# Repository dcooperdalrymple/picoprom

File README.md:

PicoPROM - DIP-EEPROM Programmer based on Raspberry Pi Pico
===========================================================

Writes ROM images to parallel-interface EEPROMs via XMODEM file transfer over USB.

|  | |  |
|:----:|----|:----:|
| Pico connected to EEPROM | | Demo video on YouTube |

Warning
-------
The Raspberry Pi Pico is not 5V-tolerant, but these EEPROMs are 5V devices.
This is fine for write-only access, but it's important to ensure the EEPROM
never writes back to the Pico's GPIO pins.  **Make sure OE is permanently wired
high, to VCC, to prevent this.**

Features
--------

* No additional components are required - just the Pico and the EEPROM
* XMODEM+CRC transfer protocol makes it easy to send files to be written to the EEPROM
* Fast operation - comparable to TL866
* Supports paged writes as well as byte-writes
* Supports write protection

Not features
------------
* Reading back and verifying is not supported and probably won't ever be
* YMODEM, ZMODEM, and other XMODEM extensions aren't supported yet

Binary Installation
-------------------
1. Without an EEPROM connected, hold BOOTSEL and connect the Raspberry Pi Pico
2. Drag picoprom.uf2 into the Raspberry Pi Pico's mass storage window
3. It should then reboot and start communicating over USB Serial

Usage
-----
1. Disconnect the Raspberry Pi Pico from power/USB
2. Wire the Raspberry Pi Pico up to the EEPROM according to the pinout table below
3. Connect the Raspberry Pi Pico to the computer by USB
4. Launch a terminal app with XMODEM support, such as Tera Term, and connect it to the Raspberry Pi Pico
5. Verify that the Raspberry Pi Pico is reporting that it's ready to receive a ROM image
7. Use your terminal to send a ROM image using the XMODEM+CRC protocol
8. Disconnect power before removing the EEPROM from the circuit

Alternatively, instead of starting the XMODEM transfer, press Enter for some configuration options and follow the instructions.

Pinout
------
The pinout is quite straightforward - the pins are laid out around the Pico in almost 
the same arrangement that they appear on the EEPROM, to make it easy and tidy to wire up.

**Make sure OE is connected high, to VCC, as allowing it to float low could cause damage to your Pico.**

| Pico pin | EEPROM pin | Function |      | Pico pin | EEPROM pin | Function |
| -------- |:----------:| -------- | ---- | -------- |:----------:| -------- |
| GP3      | 1  | A14    | | VSYS     | 28 | VCC    |
| GP4      | 2  | A12    | | GND      | 27 | WE     |
| GP5      | 3  | A7     | | GP2      | 26 | A13    |
| GP6      | 4  | A6     | | GP28     | 25 | A8     |
| GP7      | 5  | A5     | | GP27     | 24 | A9     |
| GP8      | 6  | A4     | | GP26     | 23 | A11    |
| GP9      | 7  | A3     | | VSYS     | 22 | OE     |
| GP10     | 8  | A2     | | GP22     | 21 | A10    |
| GP11     | 9  | A1     | | GP21     | 20 | CE     |
| GP12     | 10 | A0     | | GP20     | 19 | D7     |
| GP13     | 11 | D0     | | GP19     | 18 | D6     |
| GP14     | 12 | D1     | | GP18     | 17 | D5     |
| GP15     | 13 | D2     | | GP17     | 16 | D4     |
| GND      | 14 | GND    | | GP16     | 15 | D3     |

### Other options

Depending upon preference, you could swap the CE and WE connections, or connect
them both to GP21.  It doesn't make any difference to the programming
operation, I just chose this layout because it seemed most convenient to me.

If you go further and change the GP pin numbering then you'll need to update
the corresponding array in `picoprom.c`.

Cloning and Building from Source
--------------------------------
1. Set up `pico-sdk` according to the Pico's getting-started guide.
2. Clone this repository alongside `pico-sdk`
3. Create a `build` folder
4. From within the `build` folder, type: `cmake ..`
5. From within the `build` folder, type: `make`

ROM Verification Support
------------------------

In order to verify EEPROM contents after writing, an octal bus transceiver
such as the 74HC245 must be used on the data bus between the Pico and the EEPROM.
The output enable and write enable pins must also be connected to GP0 and GP1 respectively.
The direction of this transceiver is controlled by the OE pin. Please refer to the
[included schematic](hardware/assets/schematic.pdf) for appropriate wiring.

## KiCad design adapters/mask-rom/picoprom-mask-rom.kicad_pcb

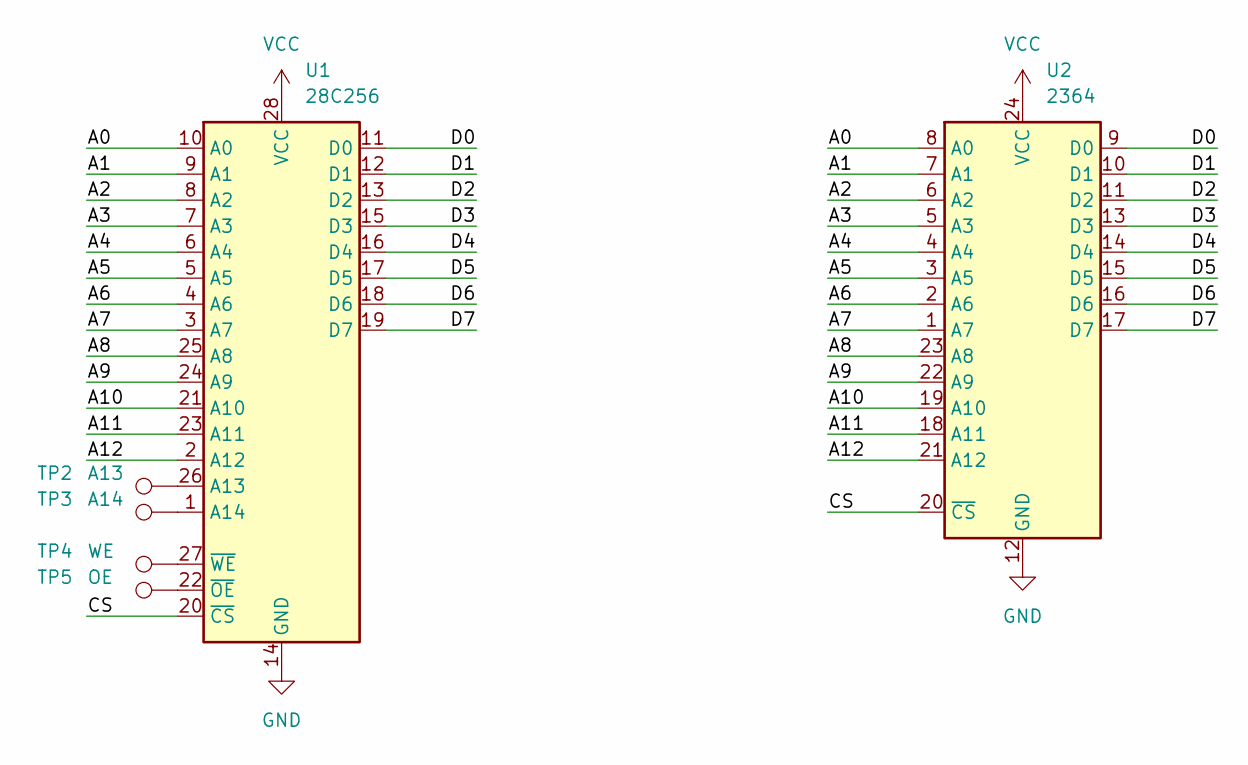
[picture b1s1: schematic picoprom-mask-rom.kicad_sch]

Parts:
TP2: A13; TestPoint_Pad_D1.0mm
TP3: A14; TestPoint_Pad_D1.0mm
TP4: WE; TestPoint_Pad_D1.0mm
TP5: OE; TestPoint_Pad_D1.0mm
U1: 28C256; PicoPROM_DIP-28_W15.24mm
U2: 2364; DIP-24_W15.24mm_Socket

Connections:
/A0: U1.10 (A0), U2.8 (A0)
/A1: U1.9 (A1), U2.7 (A1)
/A2: U1.8 (A2), U2.6 (A2)
/A3: U1.7 (A3), U2.5 (A3)
/A4: U1.6 (A4), U2.4 (A4)
/A5: U1.5 (A5), U2.3 (A5)
/A6: U1.4 (A6), U2.2 (A6)
/A7: U1.3 (A7), U2.1 (A7)
/A8: U1.25 (A8), U2.23 (A8)
/A9: U1.24 (A9), U2.22 (A9)
/A10: U1.21 (A10), U2.19 (A10)
/A11: U1.23 (A11), U2.18 (A11)
/A12: U1.2 (A12), U2.21 (A12)
/CS: U1.20 (~CS), U2.20 (~CS)
/D0: U1.11 (D0), U2.9 (D0)
/D1: U1.12 (D1), U2.10 (D1)
/D2: U1.13 (D2), U2.11 (D2)
/D3: U1.15 (D3), U2.13 (D3)
/D4: U1.16 (D4), U2.14 (D4)
/D5: U1.17 (D5), U2.15 (D5)
/D6: U1.18 (D6), U2.16 (D6)
/D7: U1.19 (D7), U2.17 (D7)
GND: U1.14 (GND), U2.12 (GND)
unnamed: TP2.1, U1.26 (A13)
unnamed: TP3.1, U1.1 (A14)
unnamed: TP5.1, U1.22 (~OE)
unnamed: TP4.1, U1.27 (~WE)
VCC: U1.28 (VCC), U2.24 (VCC)

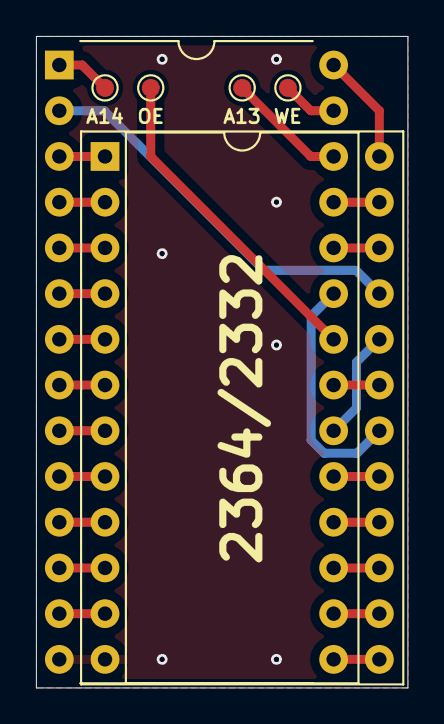
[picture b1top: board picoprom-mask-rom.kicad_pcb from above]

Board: 2 copper layers, 20.6 x 36.2 mm, 6 parts (0 on the bottom side), 28 nets.

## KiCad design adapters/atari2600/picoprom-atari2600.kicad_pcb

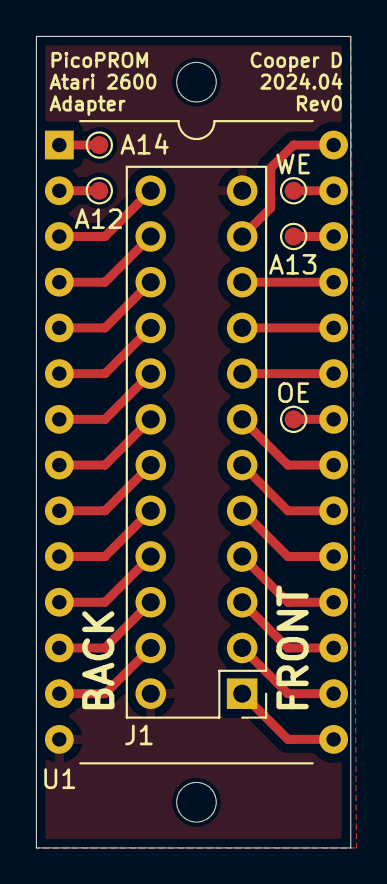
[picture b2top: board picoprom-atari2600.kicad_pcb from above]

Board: 2 copper layers, 17.5 x 45.1 mm, 7 parts (0 on the bottom side), 28 nets.

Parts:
A12: A12; TestPoint_Pad_D1.0mm
A13: A13; TestPoint_Pad_D1.0mm
A14: A14; TestPoint_Pad_D1.0mm
J1: Atari2600_Cartridge_Edge; EdgeConnector_2x12_P2.54mm_Vertical
OE: OE; TestPoint_Pad_D1.0mm
U1: 28C256; PicoPROM_DIP-28_W15.24mm
WE: WE; TestPoint_Pad_D1.0mm

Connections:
/A0: J1.20, U1.10 (A0)
/A1: J1.19, U1.9 (A1)
/A2: J1.18, U1.8 (A2)
/A3: J1.17, U1.7 (A3)
/A4: J1.16, U1.6 (A4)
/A5: J1.15, U1.5 (A5)
/A6: J1.14, U1.4 (A6)
/A7: J1.13, U1.3 (A7)
/A8: J1.10, U1.25 (A8)
/A9: J1.9, U1.24 (A9)
/A10: J1.7, U1.21 (A10)
/A11: J1.8, U1.23 (A11)
/CS: J1.6, U1.20 (~CS)
/D0: J1.21, U1.11 (D0)
/D1: J1.22, U1.12 (D1)
/D2: J1.23, U1.13 (D2)
/D3: J1.1, U1.15 (D3)
/D4: J1.2, U1.16 (D4)
/D5: J1.3, U1.17 (D5)
/D6: J1.4, U1.18 (D6)
/D7: J1.5, U1.19 (D7)
GND: J1.12, J1.24, U1.14 (GND)
unnamed: A12.1, U1.2 (A12)
unnamed: A13.1, U1.26 (A13)
unnamed: A14.1, U1.1 (A14)
unnamed: OE.1, U1.22 (~OE)
unnamed: U1.27 (~WE), WE.1
VCC: J1.11, U1.28 (VCC)

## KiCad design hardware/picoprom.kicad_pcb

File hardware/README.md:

<script type="module" src="https://kicanvas.org/kicanvas/kicanvas.js"></script>
<kicanvas-embed>
    <kicanvas-source src="picoprom.kicad_prj"></kicanvas-source>
    <kicanvas-source src="picoprom.kicad_sch"></kicanvas-source>
    <kicanvas-source src="picoprom.kicad_pcb"></kicanvas-source>
</kicanvas-embed>

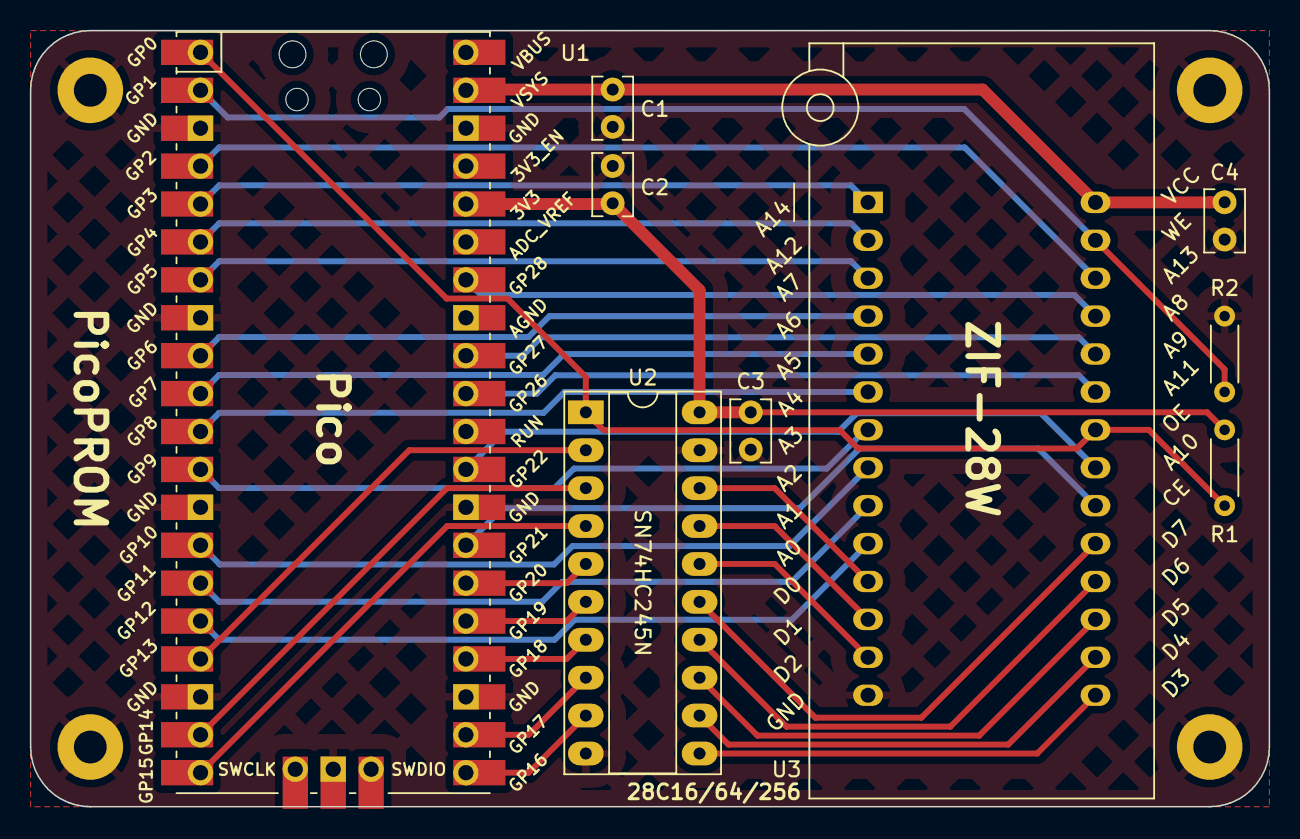
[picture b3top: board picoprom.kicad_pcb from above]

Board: 2 copper layers, 83.0 x 52.0 mm, 13 parts (0 on the bottom side), 37 nets.

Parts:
C1, C2, C3, C4: 0.1uF; C_Rect_L4.0mm_W2.5mm_P2.50mm
H1, H2, H3, H4: M2; MountingHole_2.2mm_M2_Pad
R1, R2: 47k; R_Axial_DIN0204_L3.6mm_D1.6mm_P5.08mm_Horizontal
U1: Pico; RPi_Pico_SMD_TH
U2: SN74HC245N; DIP-20_W7.62mm_Socket_LongPads
U3: 28C256; DIP_Socket-28_W11.9_W12.7_W15.24_W17.78_W18.5_3M_228-1277-0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

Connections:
+3V3: C2.1, C3.1, R1.1, U1.36 (3V3), U2.20 (VCC)
+5V: C1.1, C4.1, U1.39 (VSYS), U3.28 (VCC)
A0: U1.16 (GPIO12), U3.10 (A0)
A1: U1.15 (GPIO11), U3.9 (A1)
A2: U1.14 (GPIO10), U3.8 (A2)
A3: U1.12 (GPIO9), U3.7 (A3)
A4: U1.11 (GPIO8), U3.6 (A4)
A5: U1.10 (GPIO7), U3.5 (A5)
A6: U1.9 (GPIO6), U3.4 (A6)
A7: U1.7 (GPIO5), U3.3 (A7)
A8: U1.34 (GPIO28_ADC2), U3.25 (A8)
A9: U1.32 (GPIO27_ADC1), U3.24 (A9)
A10: U1.29 (GPIO22), U3.21 (A10)
A11: U1.31 (GPIO26_ADC0), U3.23 (A11)
A12: U1.6 (GPIO4), U3.2 (A12)
A13: U1.4 (GPIO2), U3.26 (A13)
A14: U1.5 (GPIO3), U3.1 (A14)
CE: U1.27 (GPIO21), U3.20 (~CS)
D0_3v3: U1.17 (GPIO13), U2.2 (A1)
D0_5v: U2.18 (B1), U3.11 (D0)
D1_3v3: U1.19 (GPIO14), U2.3 (A2)
D1_5v: U2.17 (B2), U3.12 (D1)
D2_3v3: U1.20 (GPIO15), U2.4 (A3)
D2_5v: U2.16 (B3), U3.13 (D2)
D3_3v3: U1.21 (GPIO16), U2.9 (A8)
D3_5v: U2.11 (B8), U3.15 (D3)
D4_3v3: U1.22 (GPIO17), U2.8 (A7)
D4_5v: U2.12 (B7), U3.16 (D4)
D5_3v3: U1.24 (GPIO18), U2.7 (A6)
D5_5v: U2.13 (B6), U3.17 (D5)
D6_3v3: U1.25 (GPIO19), U2.6 (A5)
D6_5v: U2.14 (B5), U3.18 (D6)
D7_3v3: U1.26 (GPIO20), U2.5 (A4)
D7_5v: U2.15 (B4), U3.19 (D7)
GND: C1.2, C2.2, C3.2, C4.2, H1.1, H2.1, H3.1, H4.1, R2.2, U1.3 (GND), U1.8 (GND), U1.13 (GND), U1.18 (GND), U1.23 (GND), U1.28 (GND), U1.38 (GND), U1.42 (GND), U2.10 (GND), U2.19 (OE), U3.14 (GND)
OE: R1.2, U1.1 (GPIO0), U2.1 (DIR), U3.22 (~OE)
WE: R2.1, U1.2 (GPIO1), U3.27 (~WE)

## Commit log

2024-02-16 Initial hardware design.
2024-02-19 Final edits to hardware for Rev0.
2024-02-22 Added optional support for ROM verification. [untested]
2024-03-03 Fixed bug in eeprom read routine.
2024-03-03 Added ability to read eeprom image into buffer.
2024-03-03 Allow offset in read image address.
2024-03-03 XMODEM send file procedure.
2024-03-03 Display total number of bytes during ROM verification.
2024-03-03 New action menu with read image and page options.
2024-03-03 Add page delay before verification to ensure that write process is complete.
2024-03-03 Add support for address offset in image verification.
2024-03-05 Added 3d printed case.
2024-03-27 Remove read commands if VERIFY_ROM not set.
2024-03-27 Disable automatic carriage return.
2024-03-27 Fix minor typo.
2024-03-27 Improve xmodem send transmission: No log output and better EOT response.
2024-03-27 Ignore backspaces and NAKs when not appropriate.
2024-03-27 Increase EOT timeout to 2 seconds.
2024-03-27 Cancel transmission if EOT fails.
2024-03-27 Improve xmodem send timeout verbosity.
2024-04-03 Atari 2600 cartridge reader adapter.
2024-04-18 Added additional write option commands.
2024-04-23 Menu system rewritten and project reorganized.
2024-04-23 Now assuming data writing capability. If not, leave OE and WE disconnected.
2024-04-24 Rewrite of rom communication and configuration system.
2024-04-24 Added pico-filesystem submodule
2024-04-24 Basic file system support.
2024-04-24 Switched over to using littlefs directly and fixed a number of bugs.
2024-04-25 Added general file selection routine.
2024-04-25 Updated banner for next release.
2024-04-25 Added post-delay to xmodem functions.
2024-04-25 Added file transfer action.
2024-04-25 Check for error during image writing process.
2024-04-25 Change device selection name.
2024-05-02 3d-printed cartridge connector for Atari 2600 adapter.
2024-05-02 Default to fetch Pico SDK from git.
2024-06-14 Allow device configuration to set address mask. Useful for setting upper gpio high for specific device adapters.
2024-06-14 2364/2332 Mask ROM support with passive adapter.
2024-06-14 Added changelog
2024-06-14 Global filename prompt.
2024-06-14 Direct upload command to local filesystem via XMODEM.
2024-06-14 Updated changelog.
2024-06-17 Add KiCAD preview using KiCanvas.
2024-06-17 Remove KiCanvas preview.
